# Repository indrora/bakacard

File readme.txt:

M#"""""""'M           dP                MM'""""'YMM                         dP 
##  mmmm. `M          88                M' .mmm. `M                         88 
#'        .M .d8888b. 88  .dP  .d8888b. M  MMMMMooM .d8888b. 88d888b. .d888b88 
M#  MMMb.'YM 88'  `88 88888"   88'  `88 M  MMMMMMMM 88'  `88 88'  `88 88'  `88 
M#  MMMM'  M 88.  .88 88  `8b. 88.  .88 M. `MMM' .M 88.  .88 88       88.  .88 
M#       .;M `88888P8 dP   `YP `88888P8 MM.     .dM `88888P8 dP       `88888P8 
M#########M                             MMMMMMMMMMM                            

BakaCard ("SD2PS2") is a very simple SD card to Playstation2 memory card adapter based
on the MX4SIO documentation and various parts of SD card documentation I could get my
hands on, with the goal of being easy and cheap to manufacture. 

--- "EASY" and "CHEAP" ---

Every part in this board can be sourced via LCSC. While you don't have to use LCSC,
it's a very convenient measure of "how well can I get this part."

The SD card holder chosen is a Hirose part DM3AT-SF-PEJM5. This is the *normal* version
of the one used by Trisaster. This part is 1:1 compatible with a second-source part,
the Xunpu TF-111. Their major difference is the orientation of the part off the reel for
pick and place.

LEDs are side-mounted 0603 (1608 metric) ones from Lite-On. While these don't have a
second source, a properly oriented top-fire LED will do the job. Alternatively, the
Kingbright APGA1602SEC/E/KA (digikey PN 754-1816-1-ND) will do for the red. The Green
version is APGA1602CGC/KA (754-1820-1-ND). 

All others are jellybean parts that can be sourced wherever. 

The NPN transistor has SMT pads for two different sizes, SO-23 and SO-723. It can
comfortably fit SO-523 parts as well. 

--- MANUFACTURING ---

Pick your pick & place shop. To fit this into a legit Playstation2 shell, have this made
from 1.1mm thick FR4 with either ENIG Gold or lead-free HASL. The ENIG Gold looks pretty
but comes at a higher cost. 

--- LICENSE & COPYRIGHT ---

Credit where credit is due: Takeshi did the OG hardware. I took the documentation from
Trisaster.de and redid the circuit. I'm not the only one, and others have replicated
much of the work. 

As for this design: I want as many people to have the *clean* source to this hardware.
Not just gerbers, the whole kit and kaboodle. As such, here's the ugly bit: Copyrights.

I've chosen the CERN OHL V2 Strongly Reciprocal. What's this mean? 

* You're free to make the thing, so long as you retain any notices of where to get
  the source for the thing. The silkscreen contains the GitHub URL for this project.
* If you modified it, fork my github repo and push your changes up. If I've vanished,
  do your best to put your copy of the sources up.
* If you do change things, make sure to note what you've changed. 
* Your changes will remain under the CERN OHL V2, where legally allowed.

My goal with this is not to restrict people from creating new versions of the card. The
opposite is true: I want to make sure that people can continue to refine and fix issues
with the card design.

~~ The legal bits ~~

Copyright Morgan "indrora" Gangwere and contributors, 2022

This source describes Open Hardware and is licensed under the CERN-OHL-S v2.

You may redistribute and modify this source and make products using it under
the terms of the CERN-OHL-S v2 (https://ohwr.org/cern_ohl_s_v2.txt).

This source is distributed WITHOUT ANY EXPRESS OR IMPLIED WARRANTY,
INCLUDING OF MERCHANTABILITY, SATISFACTORY QUALITY AND FITNESS FOR A
PARTICULAR PURPOSE. Please see the CERN-OHL-S v2 for applicable conditions.

Source location: https://github.com/indrora/bakacard

As per CERN-OHL-S v2 section 4, should You produce hardware based on this
source, You must where practicable maintain the Source Location visible
on the PCB. Appreciated is a link to the Source Location in user-facing
documentation, store pages, etc.

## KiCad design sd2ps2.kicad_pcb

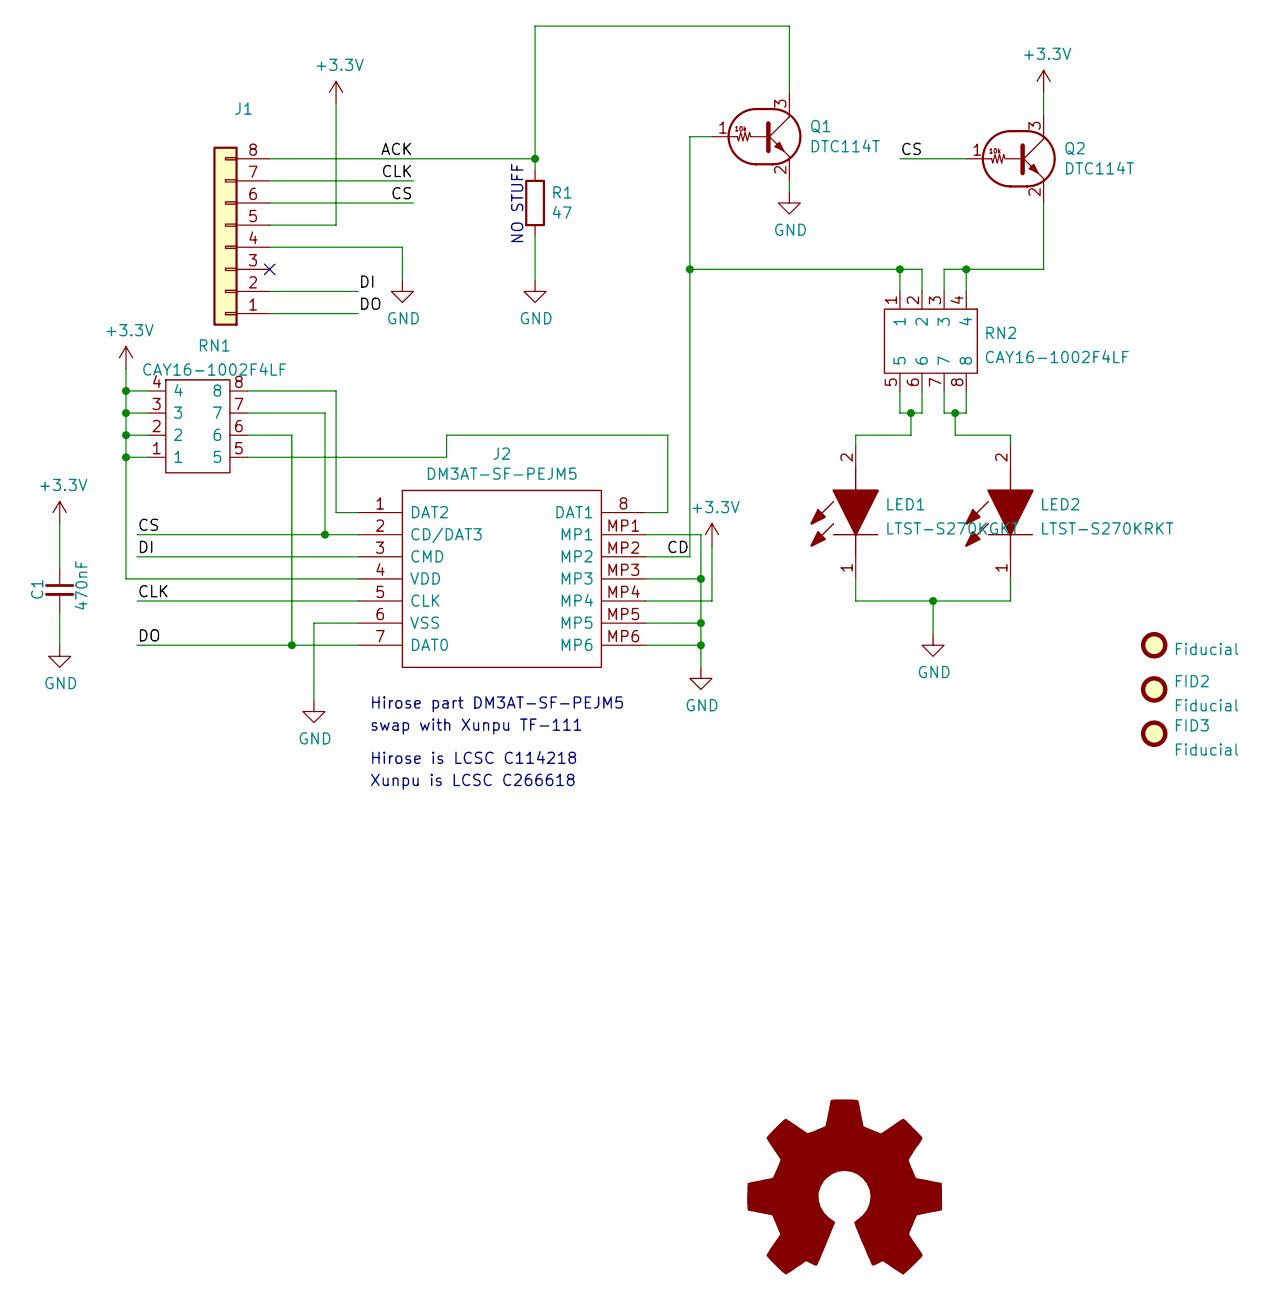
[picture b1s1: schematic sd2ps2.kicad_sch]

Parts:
C1: 470nF; C_1206_3216Metric; LCSC C29823
FID1, FID2: Fiducial; Fiducial_0.75mm_Mask1.5mm
FID3: Fiducial; Fiducial_1mm_Mask2mm
J1: PlayStation_Memory_Card
J2: DM3AT-SF-PEJM5; DM3ATSFPEJM5; Manufacturer_Part_Number DM3AT-SF-PEJM5; Mouser Part Number 798-DM3AT-SF-PEJM5
LED1: LTST-S270KGKT; LTSTS270KxKT; Manufacturer_Part_Number LTST-S270KGKT; Mouser Part Number 859-LTST-S270KGKT
LED2: LTST-S270KRKT; LTSTS270KxKT; Manufacturer_Part_Number LTST-S270KRKT; Mouser Part Number 859-LTST-S270KRKT
Q1: DTC114T; SOT-7_23Combo; LCSC C552156
Q2: DTC114T; SOT-7_23Combo; LCSC C110682
R1: 47; R_1206_3216Metric; LCSC C319585
RN1, RN2: CAY16-1002F4LF; R_Array_Convex_4x1206; Manufacturer_Part_Number CAY16-1002F4LF; Mouser Part Number 652-CAY16-1002F4LF

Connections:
+3V3: C1.1, J1.5, J2.4 (VDD), J2.MP4, Q2.3 (C), RN1.1, RN1.2, RN1.3, RN1.4
/ACK: J1.8, Q1.3 (C), R1.1
/CD: J2.MP2, Q1.1 (B), RN2.1, RN2.2
/CLK: J1.7, J2.5 (CLK)
/CS: J1.6, J2.2 (CD/DAT3), Q2.1 (B), RN1.7
/DI: J1.2, J2.3 (CMD)
/DO: J1.1, J2.7 (DAT0), RN1.6
GND: C1.2, J1.4, J2.6 (VSS), J2.MP1, J2.MP3, J2.MP5, J2.MP6, LED1.1, LED2.1, Q1.2 (E), R1.2
unnamed: J2.1 (DAT2), RN1.8
unnamed: J2.8 (DAT1), RN1.5
unnamed: LED1.2, RN2.5, RN2.6
unnamed: LED2.2, RN2.7, RN2.8
unnamed: Q2.2 (E), RN2.3, RN2.4

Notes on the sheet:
swap with Xunpu TF-111
NO STUFF
Xunpu is LCSC C266618
Hirose part DM3AT-SF-PEJM5
Hirose is LCSC C114218

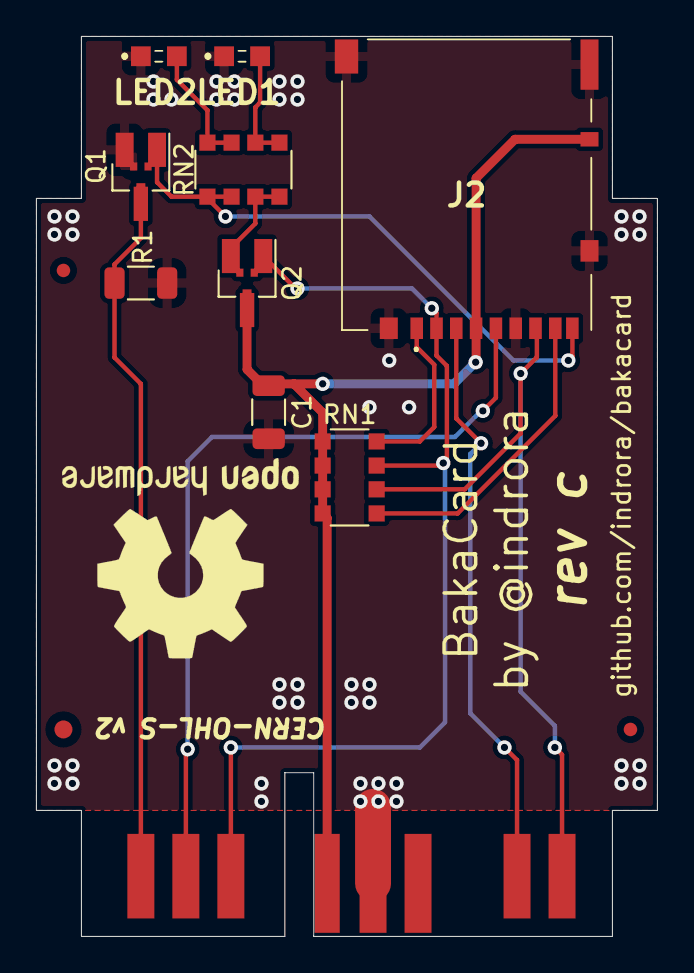
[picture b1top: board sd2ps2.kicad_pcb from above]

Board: 2 copper layers, 34.5 x 50.0 mm, 13 parts (0 on the bottom side), 13 nets.

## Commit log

2022-02-09 Fix VSS-D0 pin snafu
    I misread the instructions on the tin. Ground is important.
    also clean up some things that git doesn't need to know about in kicad's world
2022-02-11 rev b
2022-02-11 update gitignore
2022-02-11 readme and license
2022-02-11 clean up
2022-02-11 Add eratta as separate file
2022-02-17 rev c
2022-02-18 update tweaks
2022-02-18 adjust dims
